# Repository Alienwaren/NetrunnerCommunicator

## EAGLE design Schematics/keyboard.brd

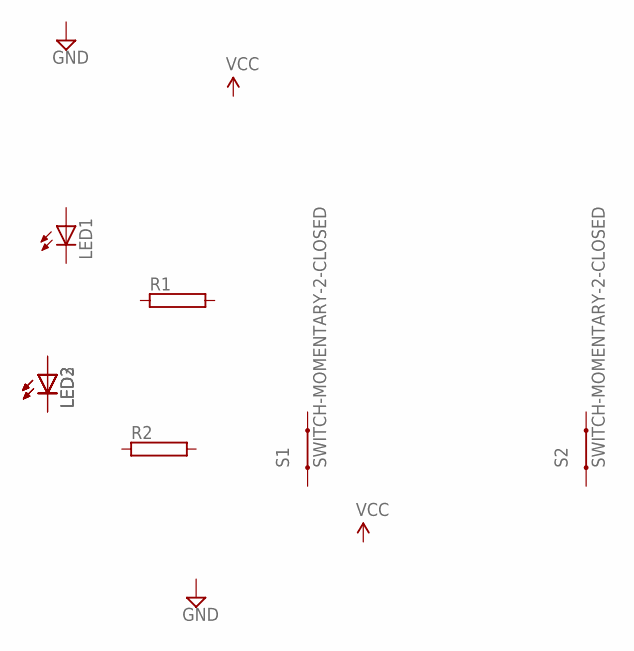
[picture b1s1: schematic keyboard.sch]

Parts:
LED1, LED2, LED3: LED_ELD260; LED_LD260
R1, R2: RAC01; AC01
S1, S2: SWITCH-MOMENTARY-2-CLOSED; TACTILE-PTH-12MM

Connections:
unnamed: LED2.A, LED3.A
unnamed: LED2.K (C), LED3.K (C)

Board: 2 copper layers, 7 parts (0 on the bottom side), 2 nets, no tracks yet.

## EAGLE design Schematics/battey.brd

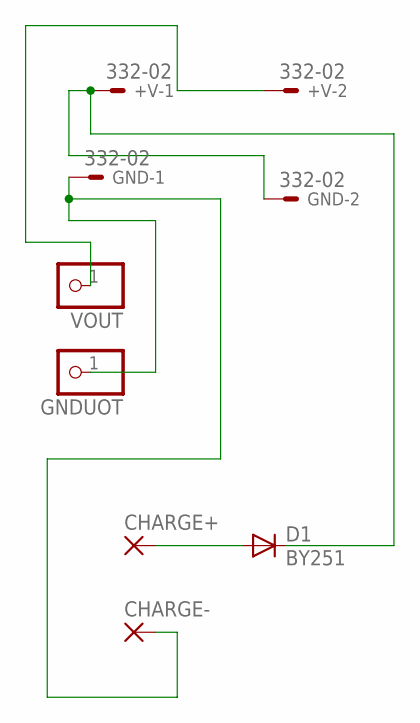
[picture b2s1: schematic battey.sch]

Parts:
+V: 332-02
CHARGE+: 2,54/1,0
CHARGE-: 2,54/1,0
D1: BY251; DO201-15
GND: 332-02
GNDUOT: PINHD-1X1; 1X01
VOUT: PINHD-1X1; 1X01

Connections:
unnamed: +V.2, VOUT.1
unnamed: CHARGE+.1, D1.A
unnamed: +V.1, D1.C, GND.2
unnamed: CHARGE-.1, GND.1, GNDUOT.1

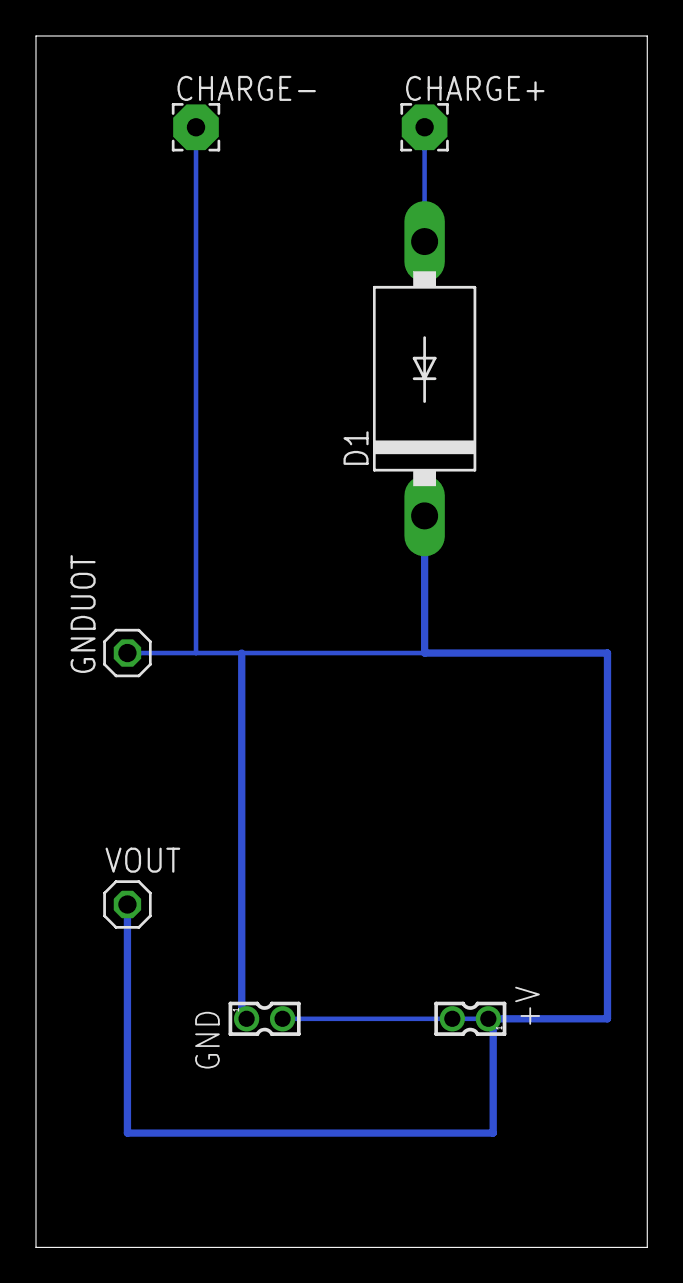
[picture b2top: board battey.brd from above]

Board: 2 copper layers, 34.0 x 67.3 mm, 7 parts (0 on the bottom side), 4 nets.

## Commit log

2014-04-13 Code Upload
    Upload all of my Code in c#
2014-04-17 Working server stub.
2014-04-25 Status bar stub
2014-05-13 Added configuration file and label pointers
2014-05-14 Added voltage class
2014-05-15 Create gh-pages branch via GitHub
2014-05-15 Changed body
2014-05-15 Google analytics
2014-05-15 image
2014-05-15 Centerimage
2014-05-15 Netrunner Hub server stub
2014-05-19 Initial and unfinished schematics
    Initial schematics of netrunner modules and solar charges wachdog
2014-05-20 Minor changes in some classes
2014-05-25 Changed Temperature Receiver
2014-05-26 Minor changes in UI

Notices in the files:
parts and their libraries:
SparkFun-Electromechanical: Licensing: Creative Commons ShareAlike 4.0 International - https://creativecommons.org/licenses/by-sa/4.0
